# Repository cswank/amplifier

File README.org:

* Amplifier
** Anodizing
https://makeitfrommetal.com/how-to-anodize-aluminum-at-home/
** Parts
*** PCB
#+CAPTION: Rev 1 of the pcb
#+NAME:   fig:PCB
[[./doc/pcb-r1.png]]

#+CAPTION: Schematic
#+NAME:   fig:Schematic
[[./doc/schematic.png]]

*** Amplifier
1ET400A
[[./doc/1ET400A - Data Sheet (1.00).pdf][Data Sheet]]
[[./doc/EVAL1 - Users Guide (1.25).pdf][User's Guide]]
[[./doc/EVAL1-SMPS1200A400 - App Note (1.00).pdf][App Note]]
*** Power Supply
SMPS1200A400
[[./doc/datasheet_hypex_SMPS1200_datasheet.pdf][Data Sheet]]
*** IR Sensor
VS1838B
[[./doc/VS1838-Infrared-Receiver-datasheet.pdf][Data Sheet]]
[[https://electronoobs.com/eng_arduino_tut34][Tutorial]]

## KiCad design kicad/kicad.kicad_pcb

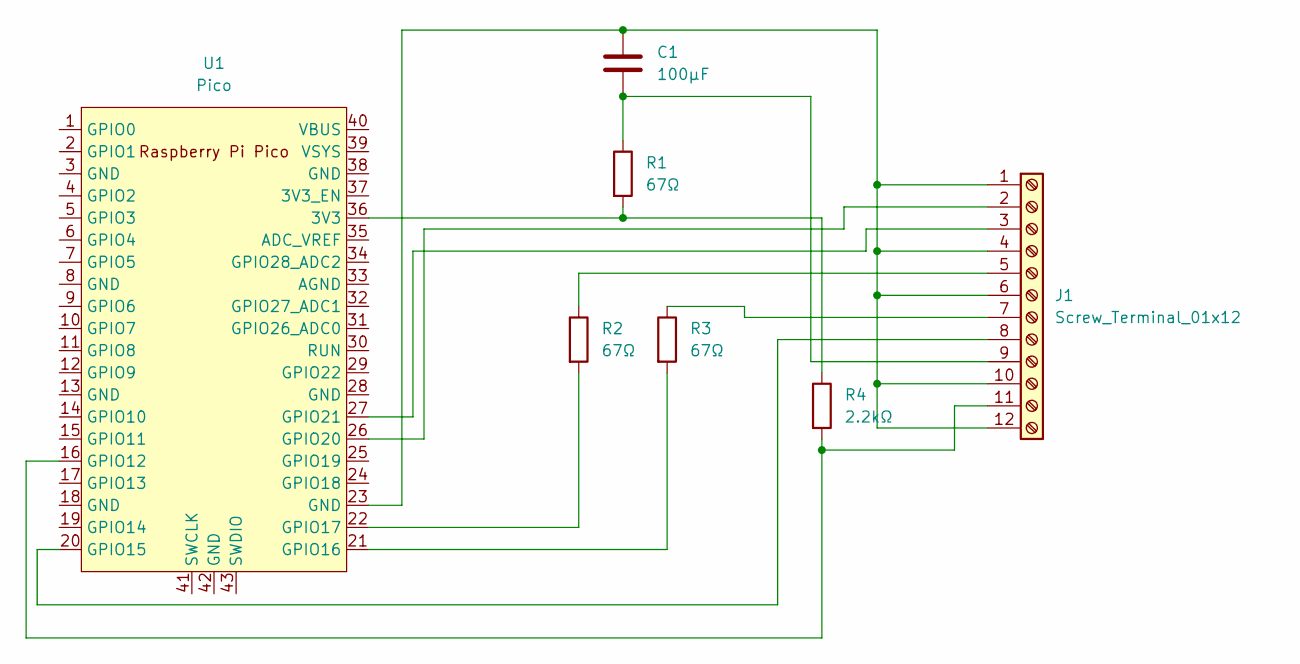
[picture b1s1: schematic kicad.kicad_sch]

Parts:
C1: 100μF; C_Disc_D7.0mm_W2.5mm_P5.00mm
J1: Screw_Terminal_01x12; terminal_block_12
R1, R2, R3: 67Ω; R_Axial_DIN0207_L6.3mm_D2.5mm_P10.16mm_Horizontal
R4: 2.2kΩ; R_Axial_DIN0207_L6.3mm_D2.5mm_P10.16mm_Horizontal
U1: Pico; RPi_Pico_SMD_TH

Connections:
unnamed: C1.1, J1.1, J1.4, J1.6, J1.10, J1.12, U1.23 (GND)
unnamed: J1.2, U1.26 (GPIO20)
unnamed: J1.3, U1.27 (GPIO21)
unnamed: J1.5, R2.1
unnamed: J1.7, R3.1
unnamed: J1.8, U1.20 (GPIO15)
unnamed: C1.2, J1.9, R1.1
unnamed: J1.11, R4.2, U1.16 (GPIO12)
unnamed: R1.2, R4.1, U1.36 (3V3)
unnamed: R3.2, U1.21 (GPIO16)
unnamed: R2.2, U1.22 (GPIO17)

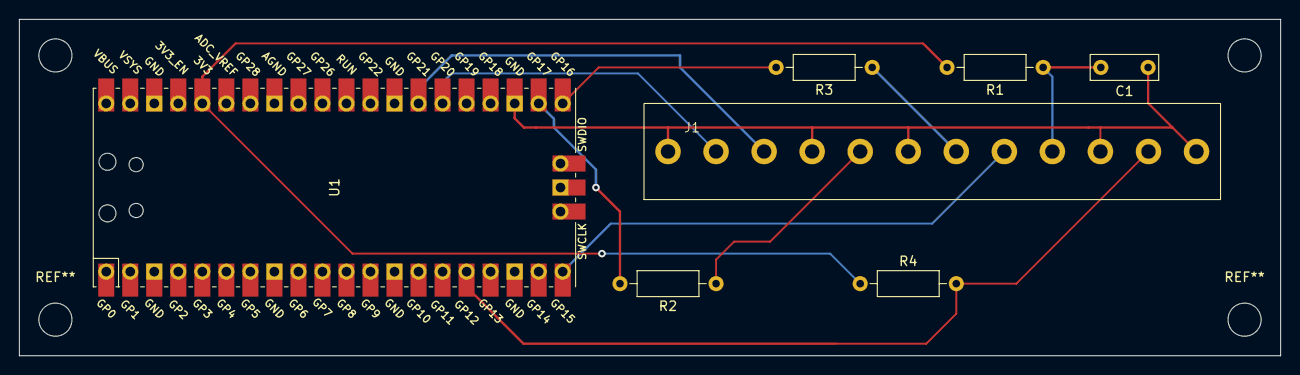
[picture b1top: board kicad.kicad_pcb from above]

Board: 2 copper layers, 133.4 x 35.6 mm, 7 parts (0 on the bottom side), 11 nets.

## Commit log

2024-02-16 add a README
2024-02-16 added some pdfs
2024-02-19 prints out duration between IR state changes
2024-02-19 format NEC logic
2024-02-19 readme changes
2024-02-20 MiniDSP 'standby' remote button detection
2024-02-20 iphone face ID uncovered a bug
    the time.Time slice was trying to write past its
    capacity (panic)
2024-02-21 unset interrupt while processing ir data
2024-02-21 alt ir parsing (doesn't work well on pico)
2024-02-21 ir.PayloadSize
2024-02-21 refactor (keep track of []time.Duration instead of []time.Time)
2024-02-21 a little cleanup of main
2024-02-21 use github.com/cswank/ir
2024-02-22 can handle hall-effect sensor for on/off too
2024-02-22 some more refactoring
2024-02-22 added pico kicad footprint submodule
2024-02-22 add some kicad stuff to gitignore
2024-02-22 gpio for power supply and amp
2024-02-22 remove pico kicad
2024-02-24 added kicad board that I'm getting printed
2024-02-24 added a pic of pcb
2024-02-24 schematic
2024-02-24 added correct schematic
2024-02-27 array instead of slice
    longer blink pulses
2024-02-28 updated cswank/ir
2024-03-03 power and amp pins start high for standby as initial state
2024-03-04 pull amp and power pins high by default
2024-03-05 update cswank/ir
2024-03-07 got rid of time.Ticker
2024-03-09 new PCB layout
2024-03-09 remove screenlog from git
2024-03-17 final kicad
2024-03-17 remove lock file
2024-04-13 add external pullup resistor
2025-12-14 switch to zig
2025-12-14 add the rest of the gpio pins
2025-12-14 comment
2025-12-14 init led
2025-12-14 led pins
2025-12-20 Update IR lib
2025-12-20 add blink firmware for testing
2025-12-20 add debug prints to blink firmware
2025-12-20 latest IR
2025-12-21 update ir dependency
